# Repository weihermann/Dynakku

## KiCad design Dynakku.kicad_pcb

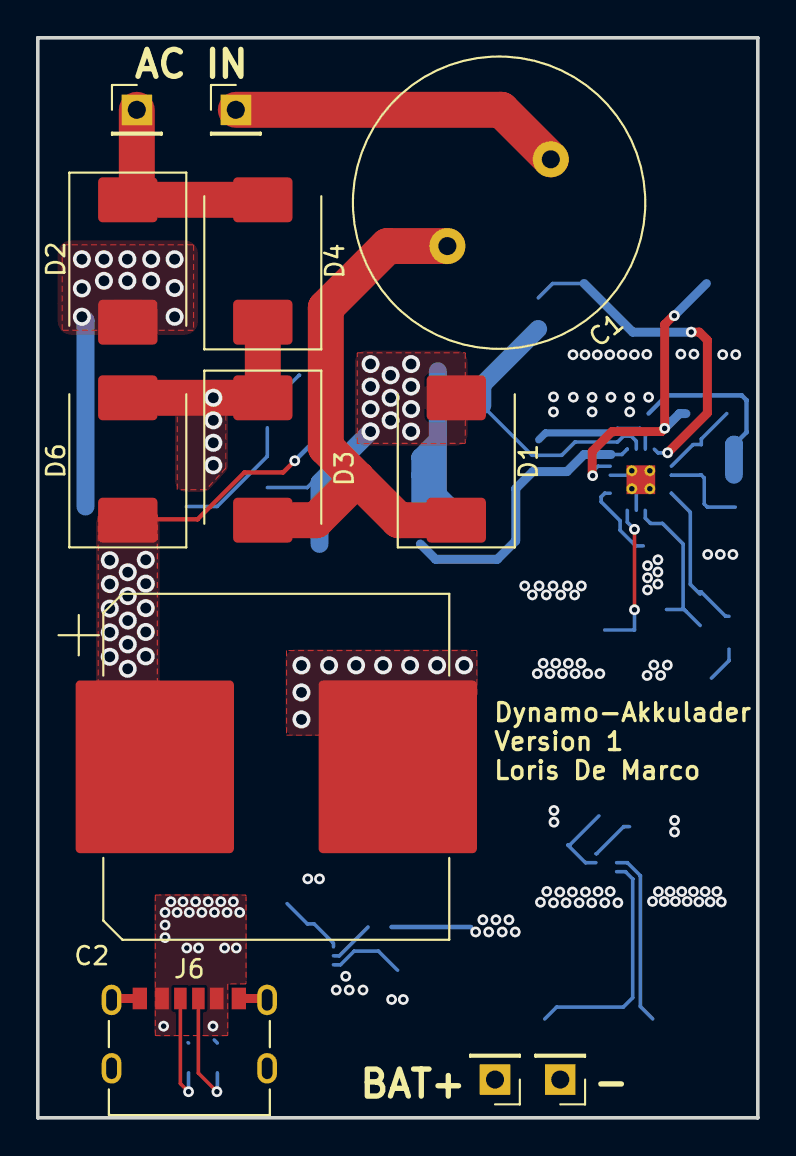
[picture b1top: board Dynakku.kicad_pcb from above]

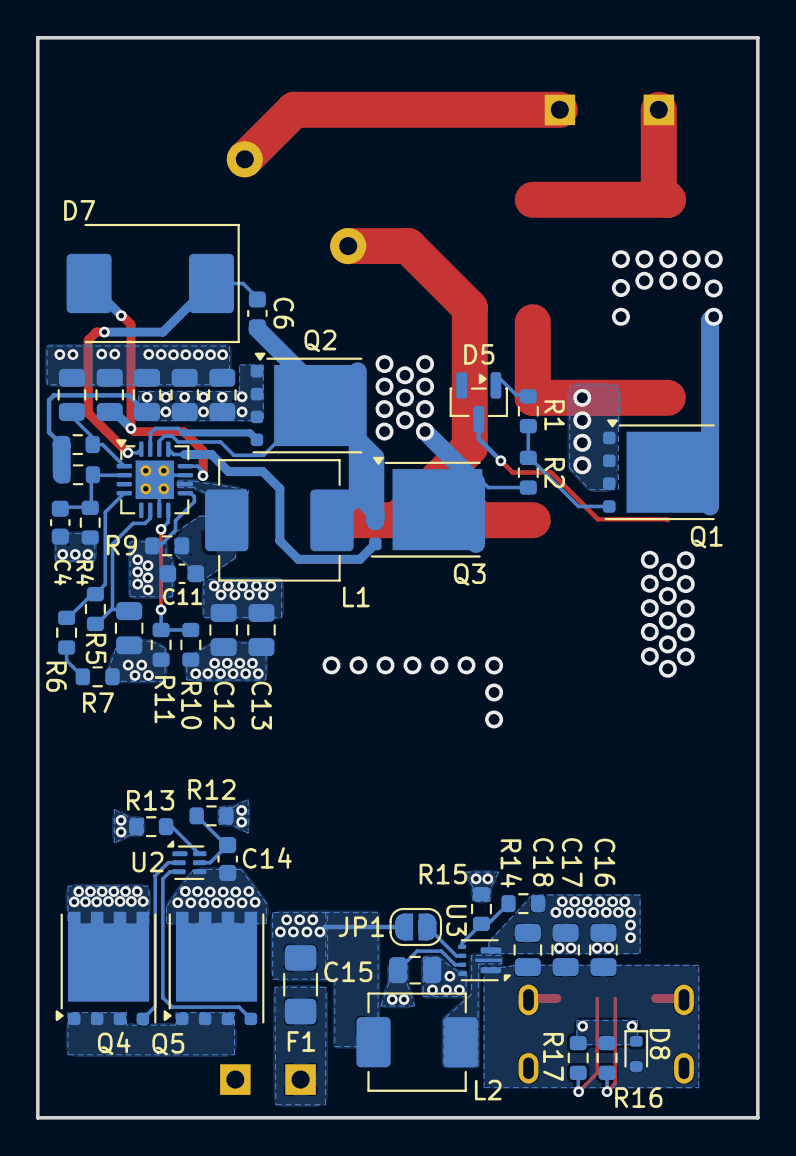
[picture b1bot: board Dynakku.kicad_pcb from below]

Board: 4 copper layers, 40.0 x 60.0 mm, 60 parts (48 on the bottom side), 34 nets.

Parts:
C1: ECE-A1HN331U, 330µ 35V; C_Radial_D16.0mm_H25.0mm_P7.50mm
C2: UUE1V102MNS6MS, 1000µ 35V; CP_Elec_18x22
C3, C5, C7, C8, C9, C10: 1µ 50V; C_0805_2012Metric
C4, C6, C11, C14: 100n 50V; C_0603_1608Metric
C12, C13, C15, C16, C17, C18: 10µ 16V; C_0805_2012Metric
D1, D2, D3, D4, D6, D7: SS34; D_SMC
D5: BZX84C20; SOT-23
D8: ESD5Z5.0; D_SOD-523
F1: 8A; Fuse_1206_3216Metric_Pad1.42x1.75mm_HandSolder
J1, J2, J4, J5: Conn_01x01_Pin; PinHeader_1x01_P2.54mm_Vertical
J6: UJC-V-G-SMT-P6-TR; SAMESKY_UJC-H-G-SMT-2-P6-TR
JP1: SolderJumper_2_Open; SolderJumper-2_P1.3mm_Open_RoundedPad1.0x1.5mm
L1: 10µ; L_Vishay_IHLP-2525
L2: IHLP2020BZER1R0M01; L_Vishay_IHLP-2020
Q1, Q2, Q3, Q4, Q5: CSD17577Q3A; VSONP-8-1EP_5x6_P1.27mm
R1, R13: 2.2k; R_0603_1608Metric
R2, R5, R6, R7, R16, R17: 10k; R_0603_1608Metric
R3, R14: 750k; R_0603_1608Metric
R4, R10, R11, R15: 100k; R_0603_1608Metric
R8: 10; R_0603_1608Metric
R9: 20m; R_0603_1608Metric
R12: 300; R_0603_1608Metric
U1: BQ24650; Texas_RVA_VQFN-16-1EP_3.5x3.5mm_P0.5mm_EP2.14x2.14mm_Therma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
U2: BQ29700; WSON-6_1.5x1.5mm_P0.5mm
U3: TPS61022; Texas_RWU0007A_VQFN-7_2x2mm_P0.5mm

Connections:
+BATT: C11.2, C12.1, C13.1, C15.1, F1.2, JP1.2 (B), L2.1, R9.2, R10.1, R12.1, U1.9 (SRN), U3.7 (VIN)
-BATT: C14.2, J5.1 (Pin_1_1), Q5.3 (S), U2.4 (VSS)
/Battery Protection/BQ29700_BAT: C14.1, R12.2, U2.5 (BAT)
/Battery Protection/BQ29700_COUT: Q4.2 (G), U2.2 (Cout)
/Battery Protection/BQ29700_DOUT: Q5.2 (G), U2.3 (Dout)
/Battery Protection/BQ29700_V-: R13.1, U2.6 (V-)
/Dynakku/AC+: C1.1, J1.1 (Pin_1_1)
/Dynakku/AC-: D2.1 (K), D4.2 (A), J2.1 (Pin_1_1)
/Interfaces/USB_CC1: J6.A5 (CC1), R16.2
/Interfaces/USB_CC2: J6.B5 (CC2), R17.2
/MPPT Charger/BQ24650_BTST: C6.2, D7.1 (K), U1.16 (BTST)
/MPPT Charger/BQ24650_HIDRV: Q2.2 (G), U1.15 (HIDRV)
/MPPT Charger/BQ24650_LODRV: Q3.2 (G), U1.13 (LODRV)
/MPPT Charger/BQ24650_MPPSET: C4.1, R3.2, R4.1, U1.2 (MPPSET)
/MPPT Charger/BQ24650_PH: C6.1, L1.1, Q2.3 (S), Q3.1 (D), U1.14 (PH)
/MPPT Charger/BQ24650_REGN: C7.1, D7.2 (A), U1.12 (REGN)
/MPPT Charger/BQ24650_SRP: C11.1, L1.2, R9.1, U1.10 (SRP)
/MPPT Charger/BQ24650_TS: R5.2, R6.1, U1.4 (TS)
/MPPT Charger/BQ24650_VCC: C5.1, R8.2, U1.1 (VCC)
/MPPT Charger/BQ24650_VFB: R10.2, R11.1, U1.8 (VFB)
/MPPT Charger/BQ24650_VREF: C3.1, R5.1, U1.6 (VREF)
/USB Boost/TPS_EN: JP1.1 (A), U3.5 (EN)
/USB Boost/TPS_FB: R14.2, R15.1, U3.4 (FB)
/USB Boost/TPS_SW: L2.2, U3.2 (SW)
GND: C2.2, C3.2, C4.2, C5.2, C7.2, C8.2, C9.2, C10.2, C12.2, C13.2, C15.2, C16.2, C17.2, C18.2, D1.2 (A), D2.2 (A), D8.2 (A), J6.A12 (GND), J6.B12 (GND), J6.SH1, J6.SH2, J6.SH3, J6.SH4, Q1.3 (S), Q3.3 (S), Q4.3 (S), R2.2, R4.2, R7.2, R11.2, R13.2, R15.2, U1.7 (TERM_EN), U1.11 (GND), U1.17 (GND), U3.1 (GND), U3.6 (MODE)
unnamed: C1.2, D1.1 (K), D3.2 (A)
unnamed: D3.1 (K), D4.1 (K), D6.2 (A), Q1.1 (D)
unnamed: D5.1 (A), R1.2
unnamed: F1.1, J4.1 (Pin_1_1)
unnamed: Q1.2 (G), R1.1, R2.1
unnamed: Q4.1 (D), Q5.1 (D)
unnamed: R6.2, R7.1
VBUS: C16.1, C17.1, C18.1, D8.1 (K), J6.A9 (VBUS), J6.B9 (VBUS), R14.1, R16.1, R17.1, U3.3 (VOUT)
VDC: C2.1, C8.1, C9.1, C10.1, D5.3 (K), D6.1 (K), Q2.1 (D), R3.1, R8.1

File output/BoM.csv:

"ID";"Bezeichner";"Footprint";"Stückzahl";"Bezeichnung";"Anbieter und Referenz";
1;"C1";"C_Radial_D16.0mm_H25.0mm_P7.50mm";1;"ECE-A1HN331U, 330µ 35V";;;
2;"C2";"CP_Elec_18x22";1;"UUE1V102MNS6MS, 1000µ 35V";;;
3;"C3, C5, C7, C8, C9, C10";"C_0805_2012Metric";6;"1µ 50V";;;
4;"C4, C6, C11, C14";"C_0603_1608Metric";4;"100n 50V";;;
5;"C12, C13, C15, C16, C17, C18";"C_0805_2012Metric";6;"10µ 16V";;;
6;"D1, D2, D3, D4, D6, D7";"D_SMC";6;"SS34";;;
7;"D5";"SOT-23";1;"BZX84C20";;;
8;"D8";"D_SOD-523";1;"ESD5Z5.0";;;
9;"F1";"Fuse_1206_3216Metric_Pad1.42x1.75mm_HandSolder";1;"8A";;;
10;"J1, J2, J4, J5";"PinHeader_1x01_P2.54mm_Vertical";4;"Conn_01x01_Pin";;;
11;"J6";"SAMESKY_UJC-H-G-SMT-2-P6-TR";1;"UJC-V-G-SMT-P6-TR";;;
12;"L1";"L_Vishay_IHLP-2525";1;"10µ";;;
13;"L2";"L_Vishay_IHLP-2020";1;"IHLP2020BZER1R0M01";;;
14;"Q1, Q2, Q3, Q4, Q5";"VSONP-8-1EP_5x6_P1.27mm";5;"CSD17577Q3A";;;
15;"R1, R13";"R_0603_1608Metric";2;"2.2k";;;
16;"R2, R5, R6, R7, R16, R17";"R_0603_1608Metric";6;"10k";;;
17;"R3, R14";"R_0603_1608Metric";2;"750k";;;
18;"R4, R10, R11, R15";"R_0603_1608Metric";4;"100k";;;
19;"R8";"R_0603_1608Metric";1;"10";;;
20;"R9";"R_0603_1608Metric";1;"20m";;;
21;"R12";"R_0603_1608Metric";1;"300";;;
22;"U1";"Texas_RVA_VQFN-16-1EP_3.5x3.5mm_P0.5mm_EP2.14x2.14mm_ThermalVias";1;"BQ24650";;;
23;"U2";"WSON-6_1.5x1.5mm_P0.5mm";1;"BQ29700";;;
24;"U3";"Texas_RWU0007A_VQFN-7_2x2mm_P0.5mm";1;"TPS61022";;;
